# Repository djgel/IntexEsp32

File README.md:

# Intex® PureSpa ESP32 control Board with Home Automation

**Control your PureSpa over MQTT for 28462, 28458 & 28457, 28561

This  software is user for hardware IntexESP32HW and used with Smart Home (optimized for [Jeedom](www.jeedom.com) & [Home Assistant](https://www.home-assistant.io)).

Codes has partial copy / inspiration of [Yogui79/IntexPureSpa] (https://github.com/Yogui79/IntexPureSpa/blob/main/README.md#hardware-to-you-need)

## Pictures & Videos
-------
- [Video - Home Assistant - Screen Recording ](https://youtu.be/5Z1keongL40)

## Hardware to you need

-   **ESP32 Dev Kit 38Pin**  (Microcontroller) -  [amazon.de](https://amzn.to/3uoa2y4) or [amazon.fr](https://amzn.to/2RvXbLn)]
-   "[**Esp32PureSpa**] (Hardware/)" Board to make! (in Developed)

## Software to you need

-   [**Arduino IDE**](https://www.arduino.cc/en/software)
-   **Install the “[ESP32 Dev Kit C 38pin](https://www.silabs.com/developers/usb-to-uart-bridge-vcp-drivers)” ** (V1 boards not  work)
-   **Install ESP32 Board for  Arduino IDE (verssion 1.0.6)  ->  [Screenshot](Docs/Image/Board-Screenshot-IDE.PNG). **
-   **Install the following libraries**  (use the Arduino Library Manager)
    -   EspMQTTClient
    -   arduino-timer
    -   WiFi (comming with Board Driver in Arduino IDE)
    -   ESPmDNS (comming with Board Driver in Arduino IDE)
    -   ArduinoOTA
-   **You need a MQTT broker**  (e.g. Mosquitto Broker)

## PureSpa Software
Now you can [Download](src/Spa/) the PureSpa code change it to your settings and upload it to your ESP or Arduino

## MQTT communication protocol

**Write your WIFI settings in this lines**

```
const char* Myssid = "YourSSID";
const char* Mypassword = "YourPassword";
```

----------

**Write your MQTT settings in this lines**

```
"YourMQTT-Broker-IP", 	  // MQTT Broker server ip
"NameMQTTBroker",        // Can be omitted if not needed
"PasswordMQTTBroker",   // Can be omitted if not needed
"IntexSpa",            // Client name that uniquely identif your device. Don't change the name!
 1883                 // The MQTT port, default to 1883. this line can be omitted
```

----------

**MQTT topic & payload**

-   Topic is the path to communtions over MQTT:  
    e.g.:  _**IntexSpa/Cmd Power on off**_
-   Payload is the command 

| Description                  | Topic String                     | Payload | Payload | Only Status           |
|------------------------------|----------------------------------|---------|---------|-----------------|
| **Power**                    | IntexSpa/Cmd Power on off        | ON=1    | OFF=0   | -               |
| **Water Filter**             | IntexSpa/Cmd water filter on off | ON=1    | OFF=0   | -               |
| **Water Filter Timer**        | IntexSpa/Cmd water filter time   | hours=2,4,6       | -   | -               |
| **Bubble**                   | IntexSpa/Cmd bubble on off       | ON=1    | OFF=0   | -               |
| **Heater**                   | IntexSpa/Cmd heater on off       | ON=1    | OFF=0   | -               |
| **Change Farenheit/Celsius** | IntexSpa/Cmd Farenheit Celsius   | F=1     | C=0     | -               |
| **Decrease the Temp.**       | IntexSpa/Cmd decrease            | UP=1    | -       | -               |
| **Increase the Temp.**       | IntexSpa/Cmd increase            | Down=1  | -       | -  
| **ESP Reset**                | IntexSpa/Cmd Reset ESP            | reset | -       | -             |  
| **Command Setpoint of Temp.**       | IntexSpa/Cmd Temperature Setpoint| "set a number"  | -       | -
| **Heater Status**                   | IntexSpa/heater state       | standby=1 & ON=2  | OFF=0    | Yes
| **Status Setpoint Temp.**         | IntexSpa/Temperature Setpoint    | -       | -       | Yes
| **Send Actual Temp 01.**        | IntexSpa/Actual Temperature01      | -       | -       | Yes             |
| **Send Actual Temp 02.**        | IntexSpa/Actual Temperature02      | -       | -       | Yes             |out
| **Send Actual Flow.**        | IntexSpa/Actual Flow      | -       | -       | Yes             |
| **Send Error Message**       | IntexSpa/Error Number            | -       | -       | Yes             |
| **Status Power on**          | IntexSpa/Power on                | -       | -       | Yes             |  
| **Status Bubble on**         | IntexSpa/Bubble on               | -       | -       | Yes             |  
| **Status Heater on**         | IntexSpa/heater on               | -       | -       | Yes             |  
| **Status Filter on**         | IntexSpa/filter on               | -       | -       | Yes             |
| **Status Filter Timer**         | IntexSpa/filter setup time               | -       | -       | Yes             |    
| **Water Jet**             |  IntexSpa/Cmd water jet on off | ON=1    | OFF=0   | -               |
| **Sanitizer**               | IntexSpa/Cmd sanitizer on off    | ON=1    | OFF=0   | -               |
| **Status Water Jet**      | IntexSpa/Water jet on          | -       | -       | Yes             |
| **Sanitizer Timer**               | IntexSpa/Cmd Sanitizer time    | hours=3,5,8    | -  | -               |
| **Status Sanitizer**        | IntexSpa/Sanitizer on            | -       | -       | Yes             |
| **Status Sanitizer Timer**        | IntexSpa/Sanitizer setup time            | -       | -       | Yes             |

## Debugging

You can debug on Arduino IDE with serial print on  **baud rate: 115200**

Options to debug  
_Uncomment to debug_  

	//#define DEBUG_RECIEVED_DATA
	//#define DEBUG_SEARCH_CHANNEL
	//#define DEBUG_SEND_COMMAND
	//#define DEBUG_PUMP_DATA
	//#define DEBUG_CONTROLER_DATA
	//#define DEBUG_CONFIG
	//#define DEBUG_MQTT
	//#define DEBUG_SEND_VALUE_TO_HOME_AUTOMATION_SW

## OTA update

You can use OTA update (wireless) via Arduino IDE after the first upload via USB.  [Screenshot](Docs/Image/Screenshot-OTA.PNG)

## Home Assistant
Is a powerful open source home automation software. [www.home-assistant.io](https://www.home-assistant.io)

You can use it as you want, I'll show you an example of a part of the files configuration.yaml and automations.yaml

**Screenshot & Video:**
1. [OFF - Whrilpool Screenshot](Docs/Image/1.HomeAssistant-OFF_Screenshot.jpg) 
2. [ON - Whrilpool Screenshot](Docs/Image/2.HomeAssistant-ON_Screenshot.jpg)
3. [Help/Infos/Reset Screenshot](Docs/Image/3.HomeAssistant-Help-Infos_Screenshot.jpg)
4. [Heat Timer](Docs/Image/4.HomeAssistant-Timer_Screenshot.jpg)
5. [Push-notification Screenshot](Docs/Image/5.HomeAssistant-Push-notification_Screenshot.jpg)
6. [Video - Screen Recording ](https://youtu.be/5Z1keongL40)

**Config of Home Assistant:** 
- [**configuration.yaml**](src/HomeAutomation/HomeAssistant/configuration.yaml)
   - Define the switches and sensors with MQTT Topics and Payload.

- [**automations.yaml**](src/HomeAutomation/HomeAssistant/automations.yaml) **(optional)**

  - All your automation settings such as push-notification on your mobile phone.

## Jeedom 

Is a powerful and innovative open source home automation software. [www.jeedom.com](https://jeedom.com/)

**Screenshot & Video:**
1. [Screenshot dashboard view](Docs/Image/10.Jeedom-Dashboard.png)
2. [Wiring video](https://www.youtube.com/watch?v=50lxF08o_vo) thanks [@Dim](https://github.com/jeedom-help-Dim-Ant)
3. Configuration video **comming soon**.

**Config of Jeedom:** 

Template for the MQTT topics are available inside the beta version from the jeedom plugin jMQTT

**On jeedom Community thread:** 

you can found some information/help (in french) on the [Jeedom Community thread](https://community.jeedom.com/t/intex-purespa-avec-commande-sans-fils/59334)

## The official Intex® PureSpa instructions

| Articel No. | English  | German   |
|-------------|----------|----------|
| 28462, 28458 & 28457, 28561    | [Download](Docs/28462-28458_344IO_202_EN_.pdf) | [Download](Docs/28462_28458_344IO_2020_DE.pdf) |

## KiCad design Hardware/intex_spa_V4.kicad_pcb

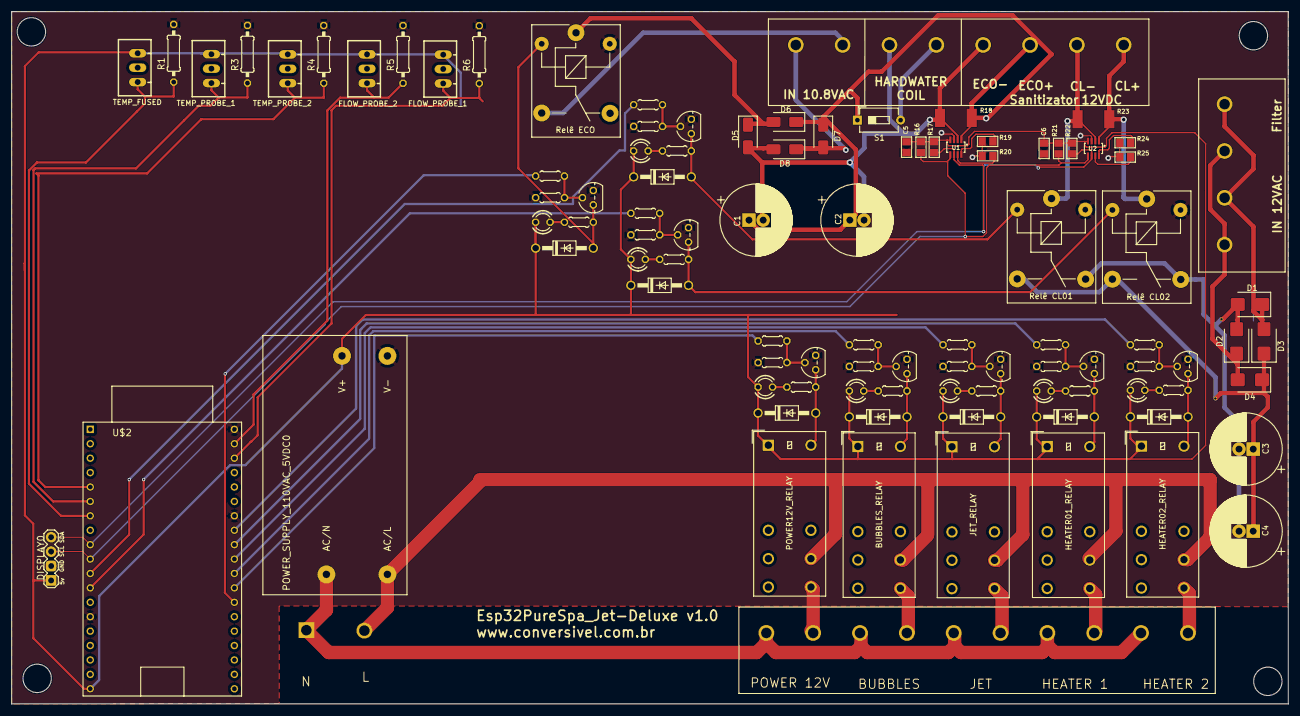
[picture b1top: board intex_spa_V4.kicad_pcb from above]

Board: 2 copper layers, 225.0 x 122.0 mm, 103 parts (0 on the bottom side), 59 nets.

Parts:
@HOLE0, @HOLE1, @HOLE2, @HOLE3: (no value)
BUBBLES_RELAY: Relay_SPDT_Omron_G2RL-1a-E; Relay_SPDT_Omron_G2RL-1-E
C1, C2, C3, C4: CP_Radial_D12.5mm_P2.50mm
C5, C6: 0.1µF; 0805
D1, D2, D3, D4: SURS8360BT3G; D_SMB
D5, D6, D7, D8#2: 1N4001; D_SMA
D8, D9, D10, D11, D12, D13, D14, D15: 1N4007; DO41-10
DISPLAY0: 4 PINS CONNECTOR; 1X04
FLOW_PROBE_1, FLOW_PROBE_2: JST-XH-3P; JST-XH-03-PACKAGE-LONG-PAD
HEATER01_RELAY, HEATER02_RELAY: Relay_SPDT_Omron_G2RL-1a-E; Relay_SPDT_Omron_G2RL-1-E
JET0: LED3MM
JET_RELAY: Relay_SPDT_Omron_G2RL-1a-E; Relay_SPDT_Omron_G2RL-1-E
LED1: LED3MM
LED_BUBBLES_RELAY: LED3MM
LED_HEATER1_RELAY, LED_HEATER2_RELAY: LED3MM
LED_RELAY_CL1, LED_RELAY_CL2: LED3MM
POWER12V_RELAY: Relay_SPDT_Omron_G2RL-1a-E; Relay_SPDT_Omron_G2RL-1-E
POWER_SUPPLY_110VAC_5VDC0: IRM-10-05; IRM_05_10
PUMP0: LED3MM
R1, R3, R4, R5, R6: 10K; 0207_10
R7, R10, R13, R24#2, R27, R30, R33, R36: 2K7; 0204_5
R8, R11, R14, R25#2, R28, R31, R34, R37: 10K; 0204_5
R9, R12, R15, R26, R29, R32, R35, R38: 150; 0204_5
R16, R17, R19, R20, R21, R22, R24, R25: 10K; 0805
R18, R23: 0.1/1% (PT2512FK-070R1L); 2512
Relê CL01, Relê CL02: Relay_SPDT_SANYOU_SRD_Series_Form_C
Relê ECO: Relay_SPDT_SANYOU_SRD_Series_Form_C
S1: SW_DIP_SPSTx01_Slide_6.7x4.1mm_W7.62mm_P2.54mm_Lo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; SW_DIP_SPSTx01_Slide_6.7x4.1mm_W7.62mm_P2.54mm_LowProfile
TEMP_FUSED: JST-XH-3P; JST-XH-03-PACKAGE-LONG-PAD
TEMP_PROBE_1, TEMP_PROBE_2: JST-XH-3P; JST-XH-03-PACKAGE-LONG-PAD
TERMINAL_BARRIER_POWER110v: 4PCV-10-006
TERMINAL_BARRIER_POWER 12V: 4PCV-04-006
TERMINAL_BARRIER_POWER 12V#2: 4PCV-08-006
T_BUBBLES_RELAY: BC547B; TO92
T_HEATER2_RELAY: BC547B; TO92
T_PUMP_RELAY0, T_PUMP_RELAY1: BC547B; TO92
T_RELAY_CL1, T_RELAY_CL2: BC547B; TO92
T_RELAY_ECO: BC547B; TO92
T__HEATER1_RELAY: BC547B; TO92
U1, U2: INA219BIDCNT; SOT23-8
U$2: ESP32-DEVKIT-C

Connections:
10.8VAC+: D5.1, D6.2, Relê ECO.1, Relê ECO.3, TERMINAL_BARRIER_POWER 12V#2.I2
10.8VAC_N: D7.2, D8#2.1, TERMINAL_BARRIER_POWER 12V#2.I1
12VAC+: D1.1, D3.2, TERMINAL_BARRIER_POWER 12V.I2, TERMINAL_BARRIER_POWER 12V.I4
12VAC_N: D2.1, D4.2, TERMINAL_BARRIER_POWER 12V.I1, TERMINAL_BARRIER_POWER 12V.I3
12VDC+: C1.1, C2.1, C3.1, C4.1, D3.1, D4.1, D6.1, D7.1, R18.2, Relê CL01.3, Relê CL02.3, S1.1, S1.2, TERMINAL_BARRIER_POWER 12V#2.I4, TERMINAL_BARRIER_POWER 12V#2.I6, U1.1
12VDC-: C1.2, C2.2, C3.2, C4.2, D1.2, D2.2, D5.2, D8#2.2, R18.1, Relê CL01.4, Relê CL02.4, TERMINAL_BARRIER_POWER 12V#2.I3, TERMINAL_BARRIER_POWER 12V#2.I5, U1.2
12VDC_CL: R23.1, R23.2, Relê CL01.1, Relê CL02.1, TERMINAL_BARRIER_POWER 12V#2.I7, TERMINAL_BARRIER_POWER 12V#2.I8, U2.1, U2.2
+5V: BUBBLES_RELAY.A1, C5.1, C6.1, D8.C, D9.C, D10.C, D11.C, D12.C, D13.C, D14.C, D15.C, DISPLAY0.1, FLOW_PROBE_1.3, FLOW_PROBE_2.3, HEATER01_RELAY.A1, HEATER02_RELAY.A1, JET0.A, JET_RELAY.A1, LED1.A, LED_BUBBLES_RELAY.A, LED_HEATER1_RELAY.A, LED_HEATER2_RELAY.A, LED_RELAY_CL1.A, LED_RELAY_CL2.A, POWER12V_RELAY.A1, POWER_SUPPLY_110VAC_5VDC0.V+, PUMP0.A, R16.2, R17.2, R21.2, R22.2, TEMP_FUSED.3, TEMP_PROBE_1.3, TEMP_PROBE_2.3, U1.4, U2.4, U$2.5V
A_BUBBLES: BUBBLES_RELAY.A2, D12.A, R29.2, T_BUBBLES_RELAY.3
A_CL_R01: D9.A, R15.2, Relê CL01.2, T_RELAY_CL1.3
A_CL_R02: D10.A, R12.2, Relê CL02.2, T_RELAY_CL2.3
A_ECO: D8.A, R9.2, Relê ECO.2, T_RELAY_ECO.3
A_HEATER_01: D14.A, HEATER01_RELAY.A2, R35.2, T__HEATER1_RELAY.3
A_HEATER_02: D15.A, HEATER02_RELAY.A2, R38.2, T_HEATER2_RELAY.3
A_JET: D13.A, JET_RELAY.A2, R32.2, T_PUMP_RELAY1.3
A_PUMP: D11.A, POWER12V_RELAY.A2, R26.2, T_PUMP_RELAY0.3
GND: C5.2, C6.2, DISPLAY0.2, POWER_SUPPLY_110VAC_5VDC0.V-, R1.2, R3.2, R4.2, R5.2, R6.2, R8.2, R11.2, R14.2, R19.1, R20.1, R24.1, R25.1, R25#2.2, R28.2, R31.2, R34.2, R37.2, Relê CL01.5, Relê CL02.5, Relê ECO.5, T_BUBBLES_RELAY.1, T_HEATER2_RELAY.1, T_PUMP_RELAY0.1, T_PUMP_RELAY1.1, T_RELAY_CL1.1, T_RELAY_CL2.1, T_RELAY_ECO.1, T__HEATER1_RELAY.1, U1.3, U2.3, U$2.GND, U$2.GND2, U$2.GND3
I1_ELT1: R20.2, U1.7
I1_ELT2: R25.2, U2.7
I2_ELT1: R19.2, U1.8
I2_ELT2: R24.2, U2.8
LEAD: BUBBLES_RELAY.11, HEATER01_RELAY.11, HEATER02_RELAY.11, JET_RELAY.11, POWER12V_RELAY.11, POWER_SUPPLY_110VAC_5VDC0.AC/L
LEAD_BUBBLES: BUBBLES_RELAY.14, TERMINAL_BARRIER_POWER110v.I4
LEAD_HEATER_1: HEATER01_RELAY.14, TERMINAL_BARRIER_POWER110v.I8
LEAD_HEATER_2: HEATER02_RELAY.14, TERMINAL_BARRIER_POWER110v.I10
LEAD_JET: JET_RELAY.14, TERMINAL_BARRIER_POWER110v.I6
LEAD_PUMP: POWER12V_RELAY.14, TERMINAL_BARRIER_POWER110v.I2
unnamed: PUMP0.K, R26.1
unnamed: JET0.K, R32.1
unnamed: LED_HEATER1_RELAY.K, R35.1
unnamed: LED_HEATER2_RELAY.K, R38.1
unnamed: R36.1, R37.1, T_HEATER2_RELAY.2
unnamed: R33.1, R34.1, T__HEATER1_RELAY.2
unnamed: R27.1, R28.1, T_BUBBLES_RELAY.2
unnamed: R30.1, R31.1, T_PUMP_RELAY1.2
unnamed: R10.1, R11.1, T_RELAY_CL2.2
unnamed: LED_RELAY_CL2.K, R12.1
unnamed: LED1.K, R9.1
unnamed: R7.1, R8.1, T_RELAY_ECO.2
unnamed: LED_RELAY_CL1.K, R15.1
unnamed: R13.1, R14.1, T_RELAY_CL1.2
unnamed: LED_BUBBLES_RELAY.K, R29.1
unnamed: R24#2.1, R25#2.1, T_PUMP_RELAY0.2
NEUTRAL: POWER_SUPPLY_110VAC_5VDC0.AC/N, TERMINAL_BARRIER_POWER110v.I1, TERMINAL_BARRIER_POWER110v.I3, TERMINAL_BARRIER_POWER110v.I5, TERMINAL_BARRIER_POWER110v.I7, TERMINAL_BARRIER_POWER110v.I9
SCL: DISPLAY0.3, R16.1, R21.1, U1.5, U2.5, U$2.IO26
SDA: DISPLAY0.4, R17.1, R22.1, U1.6, U2.6, U$2.IO25
SENSOR_FPROBE01: FLOW_PROBE_1.1, R6.1, U$2.IO22
SENSOR_FPROBE02: FLOW_PROBE_2.1, R5.1, U$2.IO23
SENSOR_TFUSE: R1.1, TEMP_FUSED.1, U$2.IO32
SENSOR_TPROBE01: R3.1, TEMP_PROBE_1.1, U$2.IO35
SENSOR_TPROBE02: R4.1, TEMP_PROBE_2.1, U$2.IO34
S_BUBBLES: R27.2, U$2.IO17
S_CL_R01: R13.2, U$2.IO27
S_CL_R02: R10.2, U$2.IO14
S_ECO: R7.2, U$2.IO4
S_HEATER_1: R33.2, U$2.IO18
S_HEATER_2: R36.2, U$2.IO19
S_JET: R30.2, U$2.IO5
S_PUMP: R24#2.2, U$2.IO16

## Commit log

2023-10-03 Docs, README, LICENSE and Organizations
2023-10-03 Adiciona o Hardware e limpeza do codigo copiado
2023-10-03 Mudanças no README
2023-10-11 Final HW Hardware
